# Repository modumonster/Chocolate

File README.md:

# Chocolate
 A low cost Eurorack PSU based on Meanwell DKA30A-12
 
 Work in progress: V1.2
 
 **Just a few photos**

 [More info here](https://modu.monster/chocolate)

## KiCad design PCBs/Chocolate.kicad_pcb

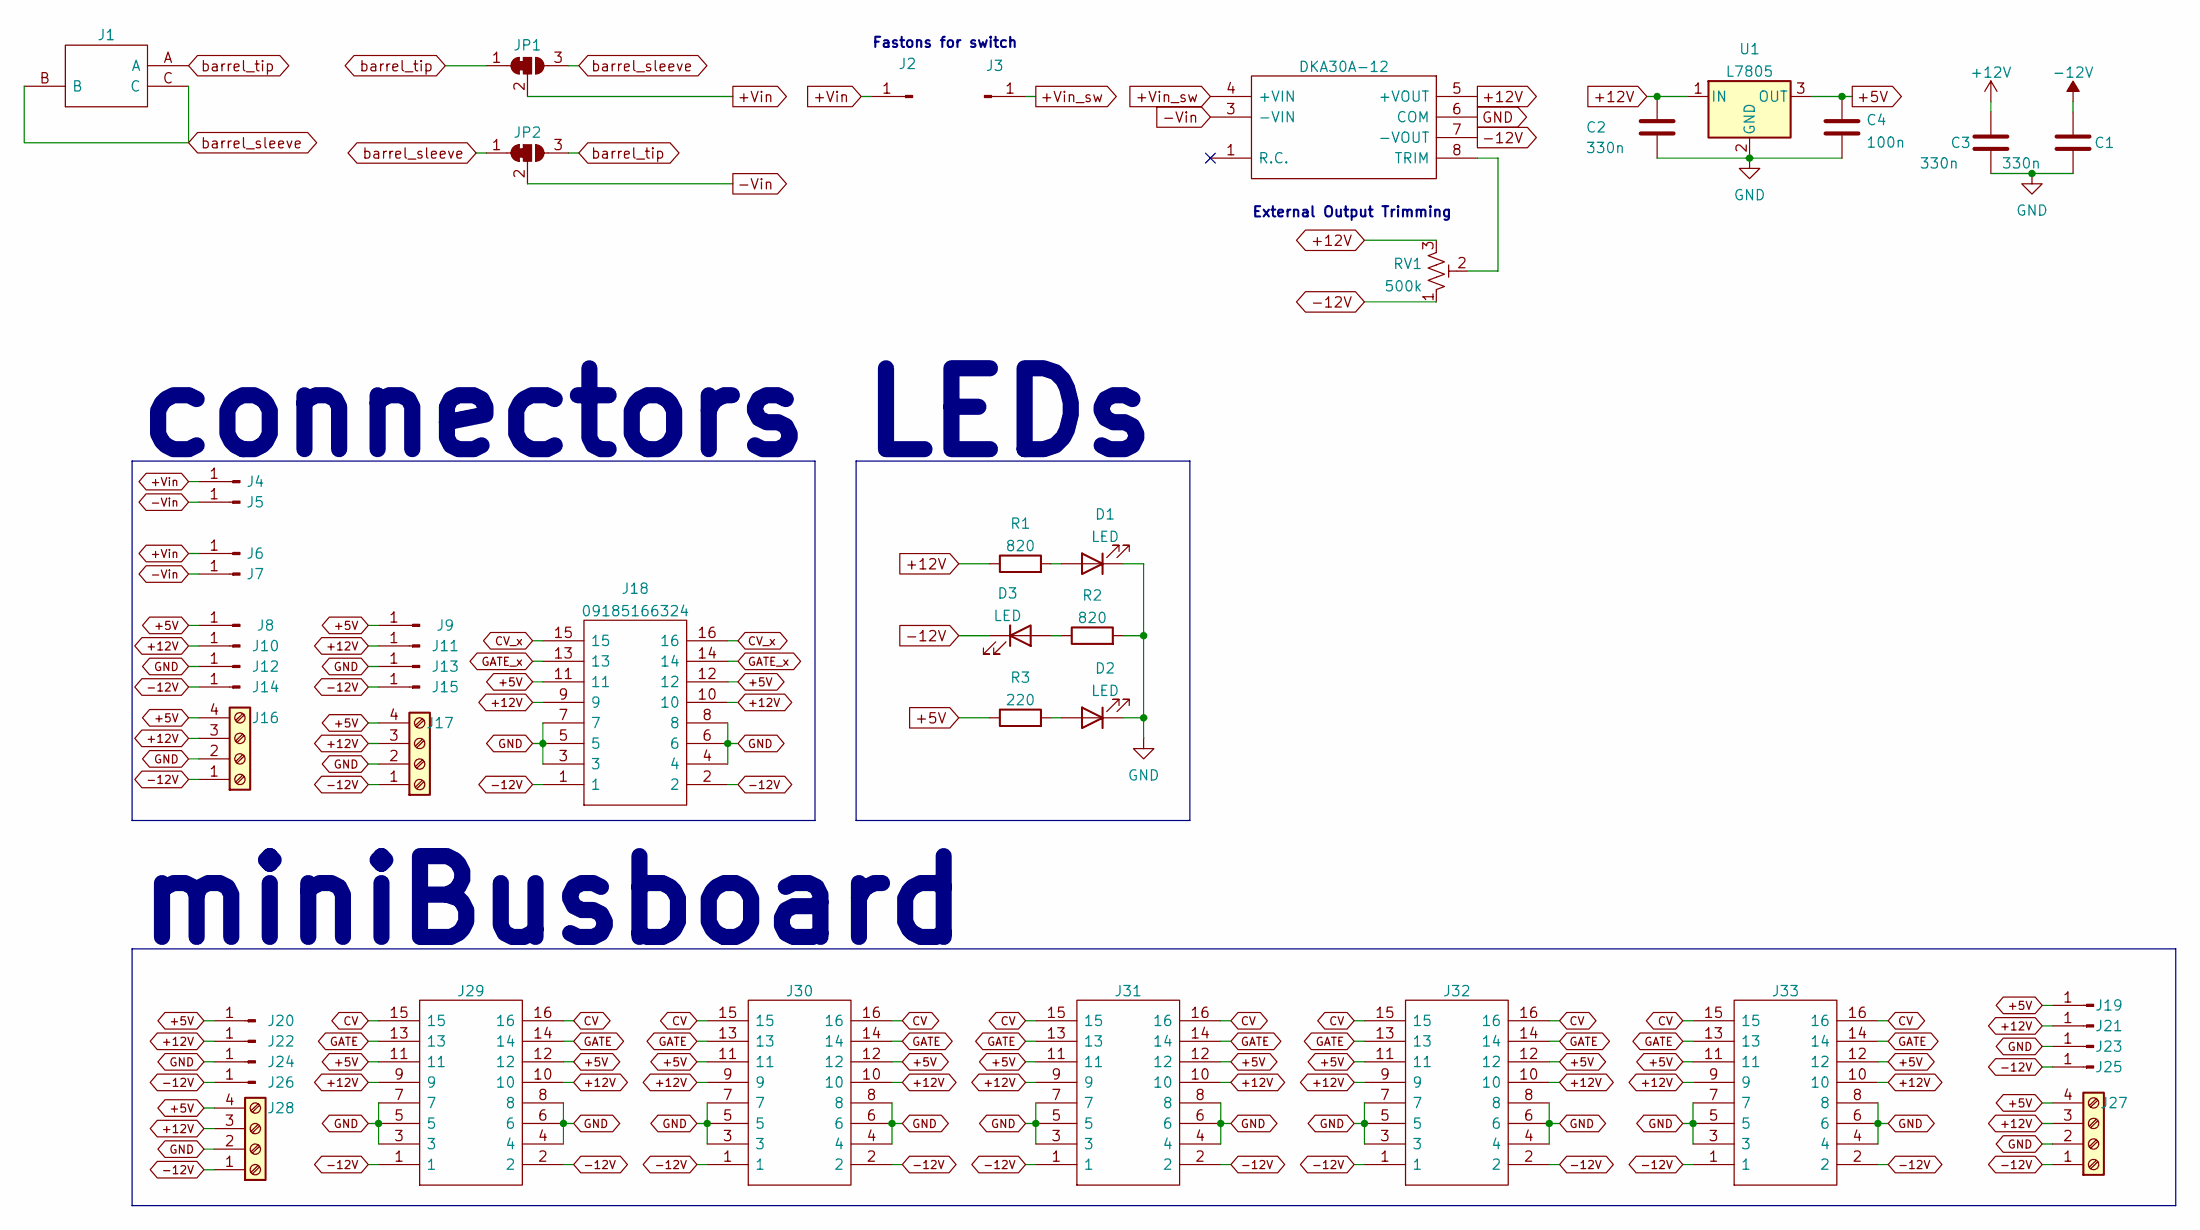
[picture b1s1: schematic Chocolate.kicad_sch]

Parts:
C1, C2, C3: 330n; C_Disc_D5.0mm_W2.5mm_P5.00mm
C4: 100n; C_Disc_D5.0mm_W2.5mm_P5.00mm
D1, D2, D3: LED; LED_D5.0mm
J1: 163-179PH-EX; 163179PHEX; Mouser Part Number 163-179PH-EX
J2, J3, J4, J5, J6, J7, J8, J9, J10, J11, J12, J13, J14, J15, J19, J20, J21, J22, J23, J24, J25, J26: Conn_01x01_Male; 23765952
J16, J17, J27, J28: Screw_Terminal_01x04; Teblock04
J18, J29, J30, J31, J32, J33: 09185166324; 16PinHeader-edgetoedge; Mouser Part Number 617-09185166324
JP1, JP2: Jumper_3_Bridged12; SolderJumper-3_P1.3mm_Bridged12_Pad-BIG
PS1: DKA30A-12; DKA30A12; Mouser Part Number 709-DKA30A-12
R1, R2: 820; R_Axial_DIN0207_L6.3mm_D2.5mm_P10.16mm_Horizontal
R3: 220; R_Axial_DIN0207_L6.3mm_D2.5mm_P10.16mm_Horizontal
RV1: 500k; Potentiometer_Bourns_3296W_Vertical
U1: L7805; TO-220-3_Horizontal_TabDown

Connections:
+5V: C4.1, J8.1, J9.1, J16.4, J17.4, J18.11, J18.12, J19.1, J20.1, J27.4, J28.4, J29.11, J29.12, J30.11, J30.12, J31.11, J31.12, J32.11, J32.12, J33.11, J33.12, R3.1, U1.3 (OUT)
+12V: C2.1, C3.1, J10.1, J11.1, J16.3, J17.3, J18.9, J18.10, J21.1, J22.1, J27.3, J28.3, J29.9, J29.10, J30.9, J30.10, J31.9, J31.10, J32.9, J32.10, J33.9, J33.10, PS1.5 (+VOUT), R1.1, RV1.3, U1.1 (IN)
+Vin: J2.1, J4.1, J6.1, JP1.2 (C)
+Vin_sw: J3.1, PS1.4 (+VIN)
-12V: C1.1, D3.1 (K), J14.1, J15.1, J16.1, J17.1, J18.1, J18.2, J25.1, J26.1, J27.1, J28.1, J29.1, J29.2, J30.1, J30.2, J31.1, J31.2, J32.1, J32.2, J33.1, J33.2, PS1.7 (-VOUT), RV1.1
-Vin: J5.1, J7.1, JP2.2 (C), PS1.3 (-VIN)
CV: J29.15, J29.16, J30.15, J30.16, J31.15, J31.16, J32.15, J32.16, J33.15, J33.16
CV_x: J18.15, J18.16
GATE: J29.13, J29.14, J30.13, J30.14, J31.13, J31.14, J32.13, J32.14, J33.13, J33.14
GATE_x: J18.13, J18.14
GND: C1.2, C2.2, C3.2, C4.2, D1.1 (K), D2.1 (K), J12.1, J13.1, J16.2, J17.2, J18.3, J18.4, J18.5, J18.6, J18.7, J18.8, J23.1, J24.1, J27.2, J28.2, J29.3, J29.4, J29.5, J29.6, J29.7, J29.8, J30.3, J30.4, J30.5, J30.6, J30.7, J30.8, J31.3, J31.4, J31.5, J31.6, J31.7, J31.8, J32.3, J32.4, J32.5, J32.6, J32.7, J32.8, J33.3, J33.4, J33.5, J33.6, J33.7, J33.8, PS1.6 (COM), R2.2, U1.2 (GND)
unnamed: D1.2 (A), R1.2
unnamed: D2.2 (A), R3.2
unnamed: D3.2 (A), R2.1
unnamed: PS1.8 (TRIM), RV1.2
barrel_sleeve: J1.B, J1.C, JP1.3 (B), JP2.1 (A)
barrel_tip: J1.A, JP1.1 (A), JP2.3 (B)

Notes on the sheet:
Fastons for switch
LEDs
External Output Trimming
miniBusboard
connectors

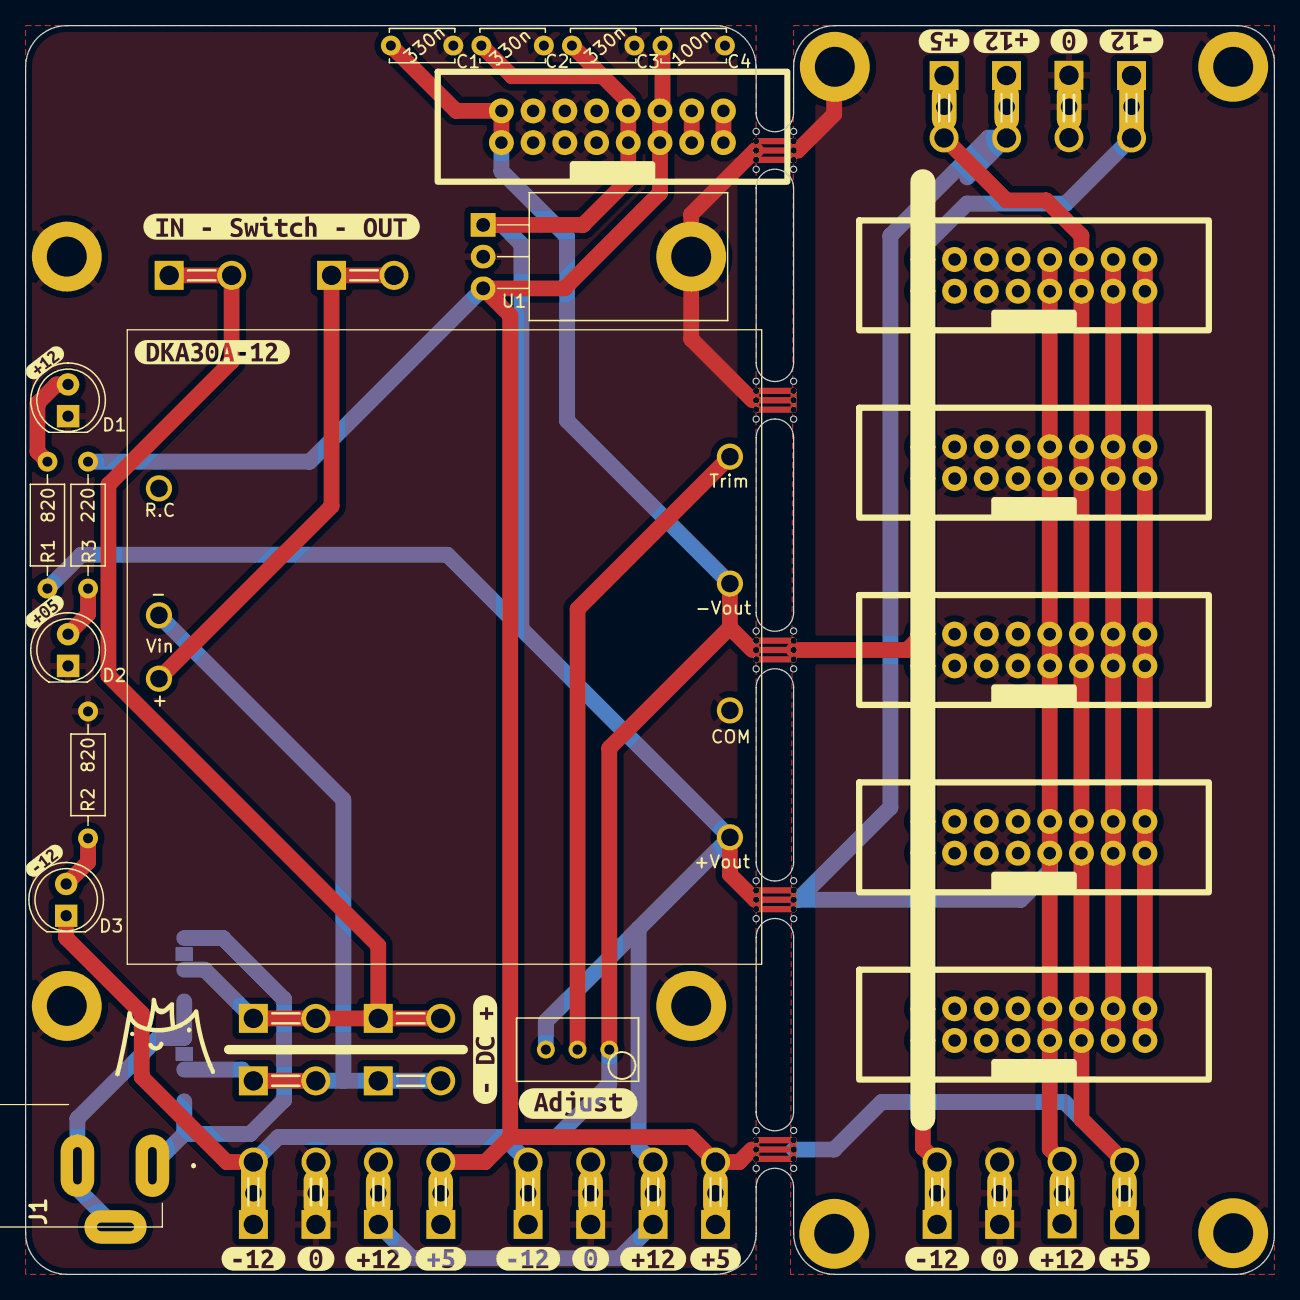
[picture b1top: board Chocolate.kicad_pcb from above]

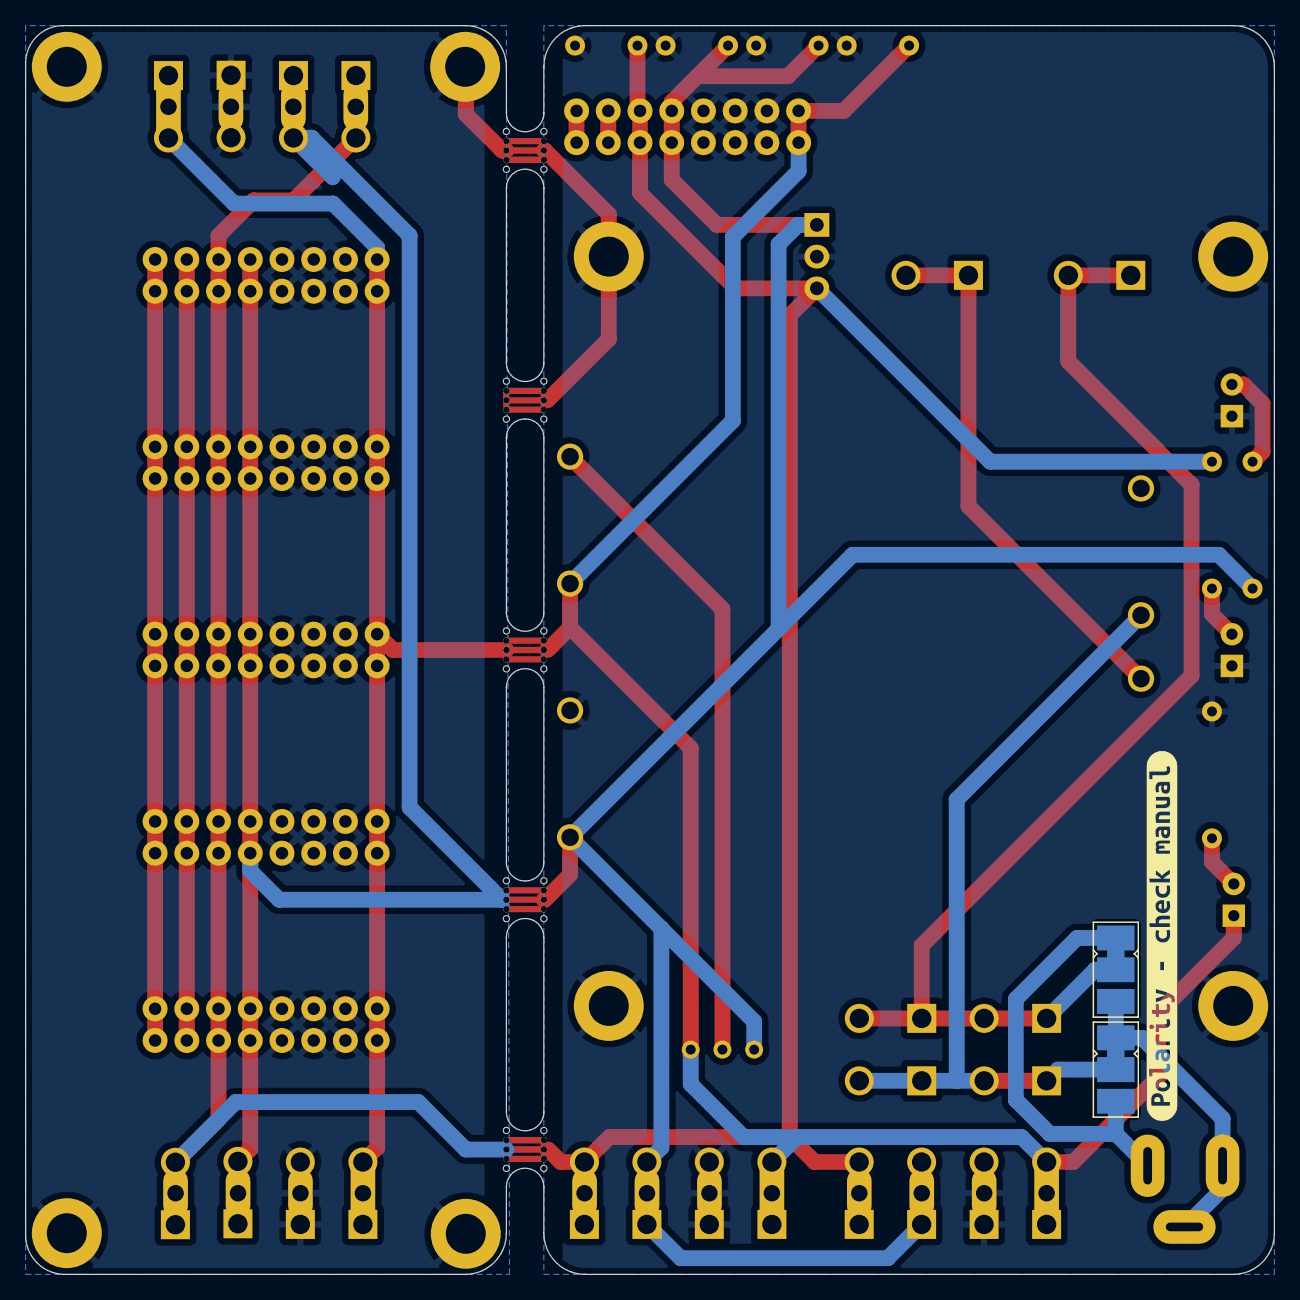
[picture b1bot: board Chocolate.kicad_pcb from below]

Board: 2 copper layers, 100.0 x 100.0 mm, 77 parts (3 on the bottom side), 17 nets.

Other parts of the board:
kibuzzard-625DD7F9, kibuzzard-625DD7F9#2, kibuzzard-625DD7F9#3, kibuzzard-625DD7F9#4: G***; kibuzzard-625DD7F9
kibuzzard-625DD823, kibuzzard-625DD823#2, kibuzzard-625DD823#3, kibuzzard-625DD823#4: G***; kibuzzard-625DD823
kibuzzard-625DD859, kibuzzard-625DD859#2, kibuzzard-625DD859#3, kibuzzard-625DD859#4: G***; kibuzzard-625DD859
kibuzzard-625DD865, kibuzzard-625DD865#2, kibuzzard-625DD865#3, kibuzzard-625DD865#4: G***; kibuzzard-625DD865
kibuzzard-6277EF73: G***; kibuzzard-6277EF73
kibuzzard-6277EFC0: G***; kibuzzard-6277EFC0
kibuzzard-62681B63: G***; kibuzzard-62681B63
kibuzzard-626819BC: G***; kibuzzard-626819BC
kibuzzard-626836F6: G***; kibuzzard-626836F6
kibuzzard-626837AF: G***; kibuzzard-626837AF
kibuzzard-62681944: G***; kibuzzard-62681944
kibuzzard-62681962: G***; kibuzzard-62681962
mouse-bite-3mm-slot, mouse-bite-3mm-slot#2, mouse-bite-3mm-slot#3, mouse-bite-3mm-slot#4, mouse-bite-3mm-slot#5: VAL**; mouse-bite-3mm-slot

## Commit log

2022-05-25 Add PCBs
    V1.2 in progress
2022-06-02 Regulator goes to sleep
    Use a different footprint for the L7805
2022-06-03 Mostly cosmetics
2022-06-03 Fix holes
2022-06-03 Add pictures, improved 3D model
